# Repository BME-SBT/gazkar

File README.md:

# BME SBT gázkar
A potméter pozíciójának megfelelő kitöltésű PWM jelet generál. A kiadott jel frekvenciája kb. 50Hz, az impulzusok szélessége 1ms és 2ms között változtatható.

## Bekötés
Felirat | Funkció
--------|--------
5V | 5V tápfeszültség
GND | föld
PWM | PWM jel kimenet, 0-5V
PB0 | [későbbi felhasználásra]
PB1 | [későbbi felhasználásra]
PB2 | engedélyezőjel; 0V:tilt, 5V:engedélyezés

## Programozás
Az ISP pineken keresztül programozható, arduinohoz hasonlóan (AVR ISP). A mikrokontroller ATtiny25.

## Debug
DEBUG_SIGNALS macroval fordítva a PB0 és PB1 pineken mérhetők az időzítések

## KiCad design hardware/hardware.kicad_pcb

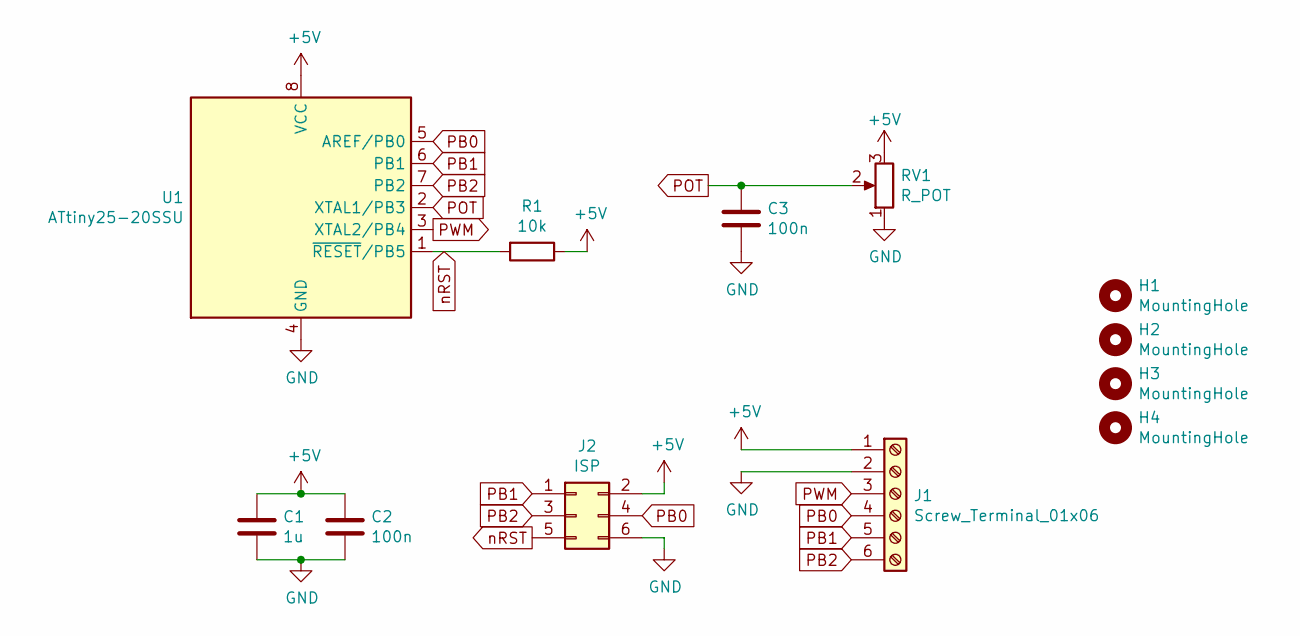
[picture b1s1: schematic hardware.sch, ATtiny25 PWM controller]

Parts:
C1: 1u; C_0805_2012Metric_Pad1.18x1.45mm_HandSolder
C2, C3: 100n; C_0805_2012Metric_Pad1.18x1.45mm_HandSolder
H1, H2, H3, H4: MountingHole; MountingHole_3.2mm_M3
J1: Screw_Terminal_01x06; TerminalBlock_Phoenix_PT-1,5-6-5.0-H_1x06_P5.00mm_Horizontal
J2: ISP; PinHeader_2x03_P2.54mm_Vertical
R1: 10k; R_0805_2012Metric_Pad1.20x1.40mm_HandSolder
RV1: R_POT; Potentiometer_Alps_RK09K_Single_Vertical
U1: ATtiny25-20SSU; SOIC-8_3.9x4.9mm_P1.27mm

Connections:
+5V: C1.1, C2.1, J1.1, J2.2, R1.1, RV1.3, U1.8 (VCC)
GND: C1.2, C2.2, C3.2, J1.2, J2.6, RV1.1, U1.4 (GND)
PB0: J1.4, J2.4, U1.5 (AREF/PB0)
PB1: J1.5, J2.1, U1.6 (PB1)
PB2: J1.6, J2.3, U1.7 (PB2)
POT: C3.1, RV1.2, U1.2 (XTAL1/PB3)
PWM: J1.3, U1.3 (XTAL2/PB4)
nRST: J2.5, R1.2, U1.1 (~RESET~/PB5)

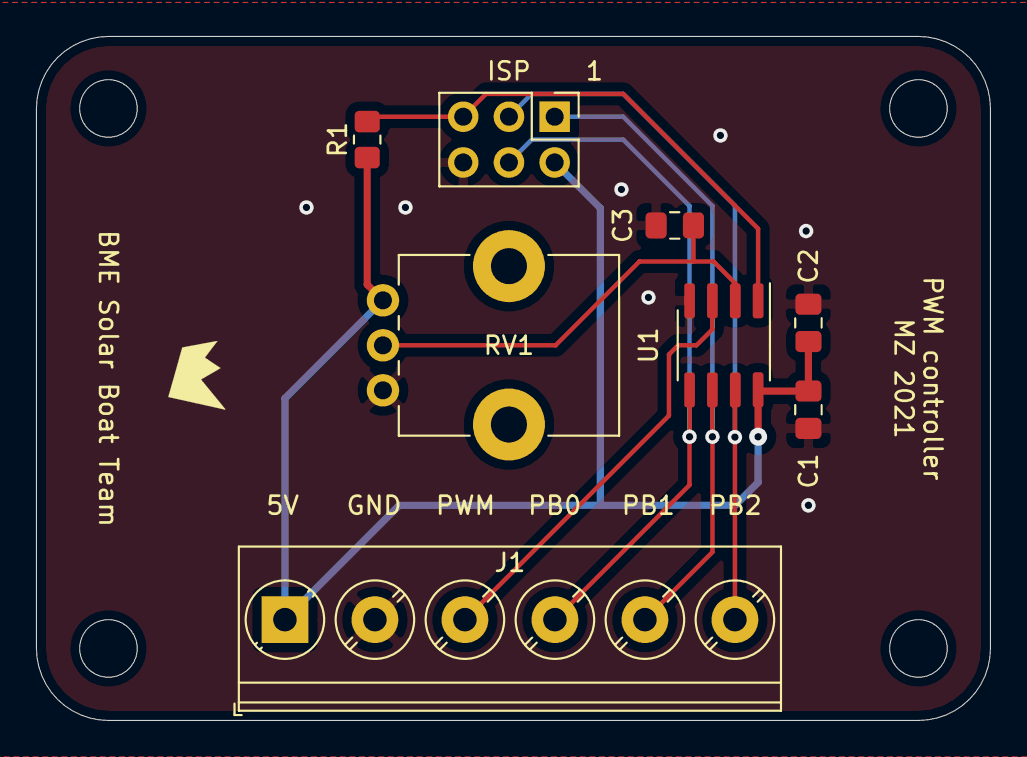
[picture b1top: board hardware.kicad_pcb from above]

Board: 2 copper layers, 53.0 x 38.0 mm, 12 parts (0 on the bottom side), 8 nets.

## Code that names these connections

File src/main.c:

/* Created by Zoltan Marcsek 08.04.2021 */
/*
 * PB3 - Potentiometer input
 * PB4 - PWM output
 * PB2 - Enable input
 */

#define ENABLE_ACTIVE_LOW 0 // Set to 0 for active high, 1 for active low
#define POT_MINIMUM 0       // Scale: 0..255
#define POT_MAXIMUM 255     // Scale: 0..255

/*
 * CLK frequency: 8MHz
 * 
 * Timer0:  interrupt every 20ms, start Timer1
 *          div=1024;clk=7.8125kHz;Cycles=156
 * 
 * Timer1:  single shot, 1-2ms impulse
 *          div=64;clk=125kHz;Cycles=125..250
 * 
 * ADC:     f_s=~4.6kHz
 *          exp. avg. filter:
 *              f_0=615Hz
 *              alpha = 0.875 (7/8)
 */

#include <avr/interrupt.h>

/*
 * If enabled:
 * PB0 will change state when a new PWM period starts
 * PB1 will change state when a new ADC sample is taken
 */
//#define DEBUG_SIGNALS

#define TC1_PRESCALER 0b0111 // Divide by 64
volatile uint8_t tim1_cmp = 255;

int main()
{
    DDRB = (1 << 4);
#ifdef DEBUG_SIGNALS
    DDRB |= (1 << 0) | (1 << 1);
#endif
    // ADC setup:
    ADMUX = 0b0011 | (1 << ADLAR); // input: PB3, left adjust, ref:VCC
    ADCSRA = (1 << ADIE) | 0b111;  // clk=62.5kHz, complete IT
    DIDR0 = (1 << 3);              // disable PB3 DIN
    ADCSRA |= (1 << ADEN);         // enable

    // Timer0 setup:
    TCCR0A = 0b10;          // CTC mode
    TCCR0B = 0b101;         // prescaler=1024
    OCR0A = 155;            // Reset at 155
    TIMSK |= (1 << OCIE0A); // Enable cmpA IT

    // Timer1 setup:
    OCR1A = tim1_cmp;
    TIMSK |= (1 << OCIE1A); // enable cmpA IT
    PLLCSR = 0;

    ADCSRA |= (1 << ADSC); // trigger ADC
    sei();

    while (1)
    {
    }
}

ISR(TIMER0_COMPA_vect)
{
    cli();
    TCCR1 |= TC1_PRESCALER; // start Timer1
    uint8_t in = ((PINB >> 2) & 0x01) ^ ENABLE_ACTIVE_LOW;
    PORTB |= (in << 4); // output ON
#ifdef DEBUG_SIGNALS
    PORTB ^= (1 << 0);
#endif
    sei();
}

ISR(TIMER1_COMPA_vect)
{
    cli();
    TCCR1 &= 0xF0;      // stop timer1
    TCNT1 = 0;          // clear
    PORTB &= ~(1 << 4); // output OFF
    OCR1A = tim1_cmp;   // set compare value
    sei();
}

ISR(ADC_vect)
{
    cli();
    uint8_t adc_scaled = ((uint16_t)(ADCH - POT_MINIMUM) * 255) / (POT_MAXIMUM - POT_MINIMUM);
    uint8_t new = (adc_scaled >> 1) | (1 << 7); // adc value -> 128..255
    uint16_t temp = (7 * new + tim1_cmp) >> 3;  // filter f_0=615Hz
    tim1_cmp = temp;
    ADCSRA |= (1 << ADSC); // trigger ADC
#ifdef DEBUG_SIGNALS
    PORTB ^= (1 << 1);
#endif
    sei();
}

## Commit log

2021-04-08 It works.
2021-04-08 Remove debug signal
2021-04-18 Add hardware
2021-07-01 things changed
2021-07-01 Add readme
